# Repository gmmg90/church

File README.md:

# Controller Campane Chiesa — ESP32

Sistema completo per il controllo automatico delle campane di una chiesa, basato su ESP32 T-Display TS0636G. Supporta programmazione settimanale, eventi speciali, controllo remoto via bot Telegram, interfaccia Web, RTC DS3231 e due relè.

**Versione firmware: v2.3.10-unified-api**

---

## Caratteristiche principali

- Web UI moderna (SPIFFS) con schede: Stato, Melodie, Programmazione, Test Relè, Impostazioni
- Bot Telegram e API HTTP unificati su layer comune `CommandHandler` (stessa logica business)
- Display TFT integrato (T-Display 135×240) con ora, data e stato sistema
- Due melodie predefinite:
  - **FUNERALE** (slot 0): 30 colpi (campana 1×3 + 2×3), 300ms suono + 2700ms pausa
  - **CHIAMATA MESSA** (slot 1): scampanio fitto alternato 1–2, 300ms + 400ms, ~100 colpi (~40s)
- Editor melodie personalizzate (fino a 120 passi)
- Programmazione settimanale e per eventi speciali (matrimoni, fest, funerali…)
- Backup/ripristino configurazione in JSON
- Pulsanti fisici esterni: FUNERALE (GPIO27) e CHIAMATA MESSA (GPIO32)
- Protezione termica con stop automatico sopra 85°C
- WiFi keepalive non-bloccante con backoff esponenziale e recovery AP
- NTP re-sync automatico ogni ora, RTC DS3231 come fallback
- Factory reset via BOOT button (tieni premuto 10s)

---

## Hardware

| Componente | Pin/Note |
|---|---|
| ESP32 T-Display TS0636G | — |
| Display TFT ST7789V 135×240 | Gestito da TFT_eSPI (pinout in `platformio.ini`) |
| RTC DS3231 | SDA=GPIO21, SCL=GPIO22 (I2C) |
| Relè Campana 1 | GPIO25 — active-low (LOW=ON) |
| Relè Campana 2 | GPIO26 — active-low (LOW=ON) |
| LED Stato | GPIO2 (LED integrato ESP32) |
| LED Feedback Melodie | GPIO33 (LED esterno, opzionale) |
| BOOT Button / Config | GPIO0 |
| Pulsante Funerale | GPIO27 — collegare a GND |
| Pulsante Messa | GPIO32 — collegare a GND |

> **Nota pin GPIO33 per LED**: nella vecchia versione era GPIO23, che coincideva con il pin TFT_RST del display. Il pin è stato corretto a GPIO33.

---

## Installazione

### 1. Configurare le credenziali

Prima di compilare, modificare `src/config.cpp`:

```cpp
const char* WIFI_SSID     = "LA_TUA_RETE_WIFI";
const char* WIFI_PASSWORD = "LA_TUA_PASSWORD_WIFI";

// Token ottenuto da @BotFather su Telegram
const char* TELEGRAM_BOT_TOKEN = "IL_TUO_TOKEN_BOT_TELEGRAM";
```

> **IMPORTANTE**: Non committare mai credenziali reali su repository pubblici. Aggiungere `src/config.cpp` al `.gitignore` se necessario.

### 2. Aggiungere utenti Telegram autorizzati

In `src/config.cpp`:

```cpp
const char* TELEGRAM_AUTHORIZED_USERS[] = {
    "123456789",   // Il tuo Chat ID (usa /start sul bot per ottenerlo)
};
const uint8_t TELEGRAM_AUTHORIZED_COUNT = 1;
```

### 3. Build e upload

In VS Code (PlatformIO):

| Task | Azione |
|---|---|
| Build firmware | `PlatformIO Build` |
| Upload firmware | `PlatformIO Upload` |
| Upload Web UI (SPIFFS) | `PlatformIO Upload FS` |
| Monitor seriale | `PlatformIO Monitor` (115200 baud) |

CLI equivalente:
```powershell
pio run -e esp32dev
pio run -e esp32dev --target upload
pio run -e esp32dev --target uploadfs
```

### 4. Primo avvio

1. Collega l'ESP32 e carica il firmware + SPIFFS.
2. Se le credenziali WiFi non sono configurate (o la connessione fallisce per 5 tentativi), il dispositivo avvia un Access Point di recovery:
   - SSID: `ChurchBells-Config`
   - Password: `campanile123`
   - Apri `http://192.168.4.1` → scheda Impostazioni → configura WiFi.
3. Al riavvio, l'IP locale appare sul display TFT e in seriale.

---

## Configurazione (file principali)

### `src/config.cpp` — Credenziali (NON committare!)
- WiFi SSID e password
- Token bot Telegram
- Lista Chat ID autorizzati

### `src/include/config.h` — Costanti sistema

| Costante | Default | Descrizione |
|---|---|---|
| `WEB_SERVER_PORT` | 80 | Porta Web UI |
| `ADMIN_USER` | `admin` | Username Basic Auth Web UI |
| `ADMIN_PASSWORD` | `LA_TUA_PASSWORD_ADMIN` | Password Basic Auth Web UI |
| `MAX_MELODY_STEPS` | 120 | Max passi per melodia |
| `BELL_MIN_PULSE` | 100ms | Impulso minimo relè |
| `BELL_MAX_PULSE` | 2000ms | Impulso massimo relè |
| `TEMP_WARNING_THRESHOLD` | 70°C | Soglia avviso temperatura |
| `TEMP_SHUTDOWN_THRESHOLD` | 85°C | Soglia stop emergenza temperatura |

---

## Bot Telegram — Comandi

| Comando | Descrizione |
|---|---|
| `/start` | Benvenuto + info autorizzazione |
| `/help` | Lista comandi |
| `/status` | Stato sistema (campane, WiFi, temperatura, uptime) |
| `/enable` / `/attiva` | Attiva campane |
| `/disable` / `/disattiva` | Disattiva campane |
| `/ring <1\|2> <ms>` | Suona campana N per X millisecondi |
| `/funeral` / `/funerale` | Avvia scampanio funerale (slot 0) |
| `/mass` / `/messa` | Avvia chiamata messa (slot 1) |
| `/melody <0-9>` | Avvia melodia per indice |
| `/schedule` / `/orari` | Prossimi eventi programmati |
| `/time` | Mostra ora/data corrente dispositivo |
| `/ntp` | Forza una resincronizzazione NTP |
| `/backup` | Mostra stato e istruzioni backup |
| `/restore` | Mostra istruzioni ripristino backup |
| `/info` | Info firmware, heap, CPU |
| `/auth` | Richiedi autorizzazione (mostra il tuo Chat ID) |

Per aggiungere un utente: dalla Web UI → Impostazioni → Telegram, oppure aggiungere il Chat ID in `config.cpp` e ricompilare.

---

## Web UI

Aprire `http://<IP-dispositivo>`. Autenticazione Basic richiesta (username/password da `config.h`).

- **Stato**: ora/data, WiFi, RTC, NTP, campane ON/OFF, test mode, temperatura, uptime
- **Melodie**: lista, riproduzione/stop, editor note (bellNumber, duration, delay)
- **Programmazione**: settimanale e eventi speciali con "programmazione semplificata"
- **Test Relè**: attivazione manuale singoli relè con durata
- **Impostazioni**: WiFi, rete IP statico/DHCP, orario manuale, backup/ripristino JSON, Telegram

---

## API REST principali

Le API sotto usano lo stesso livello comandi del bot Telegram (`CommandHandler`) per garantire coerenza dei comportamenti.

| Endpoint | Metodo | Descrizione |
|---|---|---|
| `/api/status` | GET | Stato completo sistema |
| `/api/time` | GET | Ora/data corrente |
| `/api/melodies` | GET | Lista melodie |
| `/api/melody?index=N` | GET | Dettaglio melodia N |
| `/api/test-melody` | POST | Avvia melodia `{"melodyId": N}` |
| `/api/stop-melody` | GET/POST | Stop melodia in corso |
| `/api/save-melody` | POST | Salva nuova melodia |
| `/api/update-melody` | POST | Aggiorna melodia esistente |
| `/api/delete-melody` | POST | Elimina melodia |
| `/api/weekly-schedules` | GET/POST | Programmazioni settimanali |
| `/api/special-events` | GET/POST | Eventi speciali |
| `/api/toggle-bells` | GET/POST | Abilita/disabilita campane |
| `/api/test-relay` | POST | Test relè `?relay=1&duration=500` |
| `/api/emergency-stop` | POST | Stop emergenza |
| `/api/backup` | GET | Download backup JSON |
| `/api/restore` | POST | Ripristino da JSON |
| `/api/configure-wifi` | POST | Salva WiFi e riavvia |
| `/api/set-time` | POST | Imposta ora manuale |

---

## Sicurezza

- **Credenziali WiFi e token Telegram** non devono mai essere committati su repository pubblici. Modificare sempre `src/config.cpp` prima del deploy.
- **Web UI**: protetta da Basic Auth. Le credenziali di default (`admin`/`LA_TUA_PASSWORD_ADMIN`) devono essere cambiate prima del deploy in `src/include/config.h`.
- **Bot Telegram**: solo gli utenti con Chat ID esplicitamente autorizzati possono usare i comandi. I nuovi utenti devono usare `/auth` e aspettare approvazione manuale.
- **TLS Telegram**: la connessione a `api.telegram.org` usa HTTPS. La verifica del certificato è disabilitata per default (`setInsecure()`). Per abilitarla su una rete non fidata, aggiungere il certificato root DigiCert Global Root G2:
  ```bash
  # Ottieni il certificato
  openssl s_client -connect api.telegram.org:443 -showcerts
  ```
  Poi in `telegram_bot.cpp` sostituire `setInsecure()` con `_client.setCACert(TELEGRAM_ROOT_CA_PEM)`.
- **Rete locale**: se il dispositivo deve essere raggiungibile da Internet, proteggere con VPN o reverse proxy HTTPS. Non esporre mai la Web UI direttamente su porte pubbliche.

---

## Diagnostica

Comandi disponibili via Monitor Seriale (115200 baud):

| Comando | Descrizione |
|---|---|
| `wifi_diag` | Stato WiFi dettagliato (IP, RSSI, gateway, DNS) |
| `ntp_diag` | Stato NTP/RTC (drift, ultimo sync) |
| `full_diag` | Diagnostica completa sistema |
| `temp` | Temperatura ESP32 corrente |
| `schedules` | Lista programmazioni caricate |

---

## Risoluzione problemi

| Problema | Soluzione |
|---|---|
| UI non raggiungibile | Controlla IP su display, prova `/api/status`, verifica rete |
| RTC non rilevato | Controlla cablaggio SDA/SCL, scansiona I2C con `/api/i2c-scan` (atteso 0x68) |
| Campane non suonano via Telegram | Esegui `/enable` + `/status` per verificare lo stato |
| Pulsante funerale/messa non risponde | Verifica collegamento GPIO-GND, controlla log `[FUNERAL]`/`[MASS]` in seriale |
| Display TFT non funziona | Verifica pinout in `platformio.ini`, controlla TFT_RST=23 non in conflitto con altri GPIO |
| WDT reset | Evita payload enormi senza rete stabile; il watchdog si auto-alimenta ogni 100ms |
| Restore fallisce | Verifica validità JSON; il sistema traccia contatori `imported.*` nella risposta |
| Bot Telegram non risponde | Verifica token in `config.cpp`, controlla log `[Telegram]` in seriale |
| Ore legale/solare errata | L'ora è gestita automaticamente via POSIX TZ `CET-1CEST,M3.5.0/2,M10.5.0/3` |

### Factory Reset

Tenere premuto il pulsante BOOT (GPIO0) per 10 secondi. Cancella tutta la configurazione SPIFFS (WiFi, melodie, schedules). Il firmware rimane intatto.

---

## Changelog

| Versione | Novità |
|---|---|
| v2.3.10 | Unificazione Telegram + HTTP tramite `CommandHandler`, nuove azioni Telegram `/time` `/ntp` `/backup` `/restore` |
| v2.3.9 | Bot Telegram con autenticazione whitelist, comandi remoti campane |
| v2.3.8 | Sistema recovery multilivello: DHCP fallback, AP mode dopo 5 fail WiFi |
| v2.3.7 | Protezione picchi tensione, soft-start relè, LED feedback melodie (GPIO33) |
| v2.3.6 | Refactoring schedules unificati (schedules.json) |
| v2.3.5 | WatchdogManager, WiFiReconnectManager, gestione errori strutturata |
| v2.3.2 | Performance Web UI, ottimizzazioni memoria |
| v2.3.1 | Anti-flicker UI, throttling API, CSS anti-FOUC |
| v2.3.0 | WiFi keepalive 30s, NTP re-sync orario, fix melodie interrotte |

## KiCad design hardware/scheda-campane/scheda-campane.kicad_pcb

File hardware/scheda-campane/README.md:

# Scheda base campane v1.0 (T-Display + 24 V)

Circuito stampato 100 × 80 mm su cui si innesta il **LilyGO T-Display ESP32**. La scheda:

- si alimenta a **24 VDC**, con fusibile ripristinabile, protezione dall'inversione di polarità e soppressore di picchi (TVS); un convertitore DC-DC K7805-1000R3 (ingresso 8–36 V) ricava i 5 V;
- pilota **4 uscite a 24 V** tramite ULN2003: 2 campane più 2 di riserva, ciascuna con LED. Le uscite sono **spente** quando l'ESP32 è spento, in reset o in programmazione;
- legge **4 ingressi optoisolati a 24 V**: FUNERALE, MESSA e 2 di riserva, ciascuno con LED;
- ha l'**orologio DS3231M integrato** (stessi registri del DS3231: il firmware non cambia) con batteria tampone CR2032;
- ha uno **zoccolo per il T-Display** con l'USB-C sul bordo, per programmarlo senza smontarlo, e la zona dell'antenna WiFi senza rame.

Sulla scheda arrivano solo 24 V: **niente 230 V**. I 230 V restano nel quadro elettrico.

| Lato componenti | Montaggio |
|---|---|
|  |  |

Schema elettrico: [`docs/schema-elettrico.pdf`](docs/schema-elettrico.pdf). Controllo DRC: [`docs/drc-report.txt`](docs/drc-report.txt) (0 errori, 0 collegamenti mancanti).

## File

| File | A cosa serve |
|---|---|
| `produzione/scheda-campane-gerber-jlcpcb.zip` | Gerber + forature, da caricare su JLCPCB |
| `produzione/scheda-campane-BOM-jlcpcb.csv` | Distinta materiali con i codici LCSC |
| `produzione/scheda-campane-CPL-jlcpcb.csv` | Posizione e rotazione dei componenti per il montaggio |
| `scheda-campane.kicad_pro/.kicad_pcb/.kicad_sch` | Progetto KiCad (si apre con KiCad 7 o successivi) |
| `tools/` | Script che rigenerano tutto (vedi in fondo) |

## Ordinare su JLCPCB

1. Su jlcpcb.com scegli **Order now** e carica lo zip dei Gerber. Lascia le impostazioni standard: 2 strati, FR-4, 1,6 mm, rame 1 oz. Quantità minima: 5 schede.
2. Attiva **PCB Assembly**, lato **Top**, tipo **Standard**. Lo Standard serve perché ci sono componenti a foro passante: morsetti, connettori del T-Display e convertitore DC-DC. Scegli quante schede montare (minimo 2).
3. Carica la **BOM** e il **CPL**. JLCPCB abbina i componenti tramite la colonna `LCSC Part #`.
4. **Controlla l'anteprima del montaggio**, componente per componente. Per alcuni package lo zero di rotazione di JLCPCB è diverso da quello di KiCad. Se un componente appare ruotato, correggilo nell'anteprima con il tasto di rotazione. Verifica in particolare:
   - **D1, D3** (SS34), **D2** (SMBJ33A), **D4–D7** (1N4148W): la banda del catodo deve coincidere con la banda disegnata sulla serigrafia;
   - **LED1–LED10**: catodo verso il segno della serigrafia;
   - **U2** (ULN2003), **U7** (DS3231M), **U3–U6** (optoisolatori): il pallino del pin 1 sul segno del pin 1;
   - **BT1** (portabatteria CR2032).
5. La **batteria CR2032** non viene montata da JLCPCB: va comprata a parte e inserita.

Prima di ordinare, stampa `docs/scheda-montaggio.png` in **scala 1:1** (100 × 80 mm) e appoggia il T-Display sui due connettori, per controllare che le misure coincidano.

### Costi e come risparmiare

Componenti per 5 schede: circa **48 $** (circa 9,7 $ a scheda, prezzi JLCPCB di novembre 2026). Si aggiungono i 3 $ di caricamento per ogni tipo di componente "Extended" (8 tipi), il circuito stampato, il montaggio e la spedizione.

Per spendere ancora meno:
- **Saldare tu i componenti a foro passante**: morsetti J1–J9, connettori J10–J11 e convertitore U1, circa 30 saldature. Nella BOM di JLCPCB togli la spunta a queste righe e compra i pezzi su LCSC con gli stessi codici. Eviti il costo del montaggio manuale di JLCPCB e 3 tipi "Extended".
- **Non montare i canali di riserva**, se non ti servono: togli la spunta a J4, J5, J6, J7, R8, R9, LED4, LED5, U3, U4, R10, R11, LED6, LED7, D4, D5, R14, R15, C5, C6. Il resto della scheda funziona uguale.

## Collegamenti nel quadro

```
Alimentatore 24 VDC ──► J1 "+24V" / "0V"

USCITE (J2..J5)                      RELÈ D'INTERFACCIA 24 VDC (es. Finder 38.51)
  morsetto "+24V" ─────────────────► A1 (+)
  morsetto "OUT"  ─────────────────► A2 (−)
                                      11 (COM) ◄── L 230 V (dopo il fungo d'emergenza)
                                      14 (NA)  ──► A1 bobina teleruttore Schneider ── A2 ── N
                                                   (soppressore RC sulla bobina; varistore sul martello)

INGRESSI (J6..J9)
  morsetto "+24V" ── pulsante (contatto NA) ── morsetto "IN"
```

| Morsetto | Funzione | GPIO |
|---|---|---|
| J1 | Alimentazione 24 VDC | — |
| J2 | CAMPANA 1 | GPIO25 |
| J3 | CAMPANA 2 | GPIO26 |
| J4 | USCITA 3 (riserva) | GPIO33 |
| J5 | USCITA 4 (riserva) | GPIO17 |
| J9 | FUNERALE | GPIO27 |
| J8 | MESSA | GPIO32 |
| J6 | IN 3 (riserva) | GPIO36 |
| J7 | IN 4 (riserva) | GPIO39 |

Ogni uscita regge fino a 500 mA (corrente totale limitata dal fusibile da 1,1 A). I relè d'interfaccia da 24 V assorbono pochi mA.

## Firmware

Con questa scheda le uscite sono **attive HIGH** (in passato erano moduli relè attivi LOW). Compila e carica con l'ambiente dedicato:

```bash
pio run -e scheda_v1 --target upload
```

L'ambiente `esp32dev` resta per il vecchio cablaggio con moduli relè attivi LOW. Gli ingressi non cambiano: premendo il pulsante il GPIO va a livello basso, come prima.

## Avvertenze

- Il progetto ha superato il controllo automatico delle regole di KiCad (DRC) ed è stato verificato che schema e circuito stampato abbiano gli stessi collegamenti. **Non è ancora stato provato fisicamente**: ordina prima poche schede e collaudale. Una revisione da parte di un tecnico elettronico è consigliata.
- La parte a 230 V del quadro (teleruttori, relè d'interfaccia, fungo) va realizzata da un elettricista abilitato (DM 37/08).
- Le piste sono state tracciate da uno script automatico (`tools/router.py`). Il risultato è corretto elettricamente ma meno "elegante" di un tracciato fatto a mano. Puoi rifinirlo in KiCad.

## Rigenerare i file

Servono KiCad 7 (con `pcbnew` per Python e `kicad-cli`) e, per le immagini, Node.js con Playwright.

```bash
/usr/bin/python3 hardware/scheda-campane/tools/make.py
```

Lo script esegue: `board_def.py` (componenti, collegamenti, posizioni) → `build.py` (circuito stampato) → `router.py` (piste e piani di massa) → DRC → `export.py` (file JLCPCB) → `sch_gen.py` (schema) → verifica schema/PCB → immagini. Per modificare la scheda, cambia `board_def.py` e rilancia.

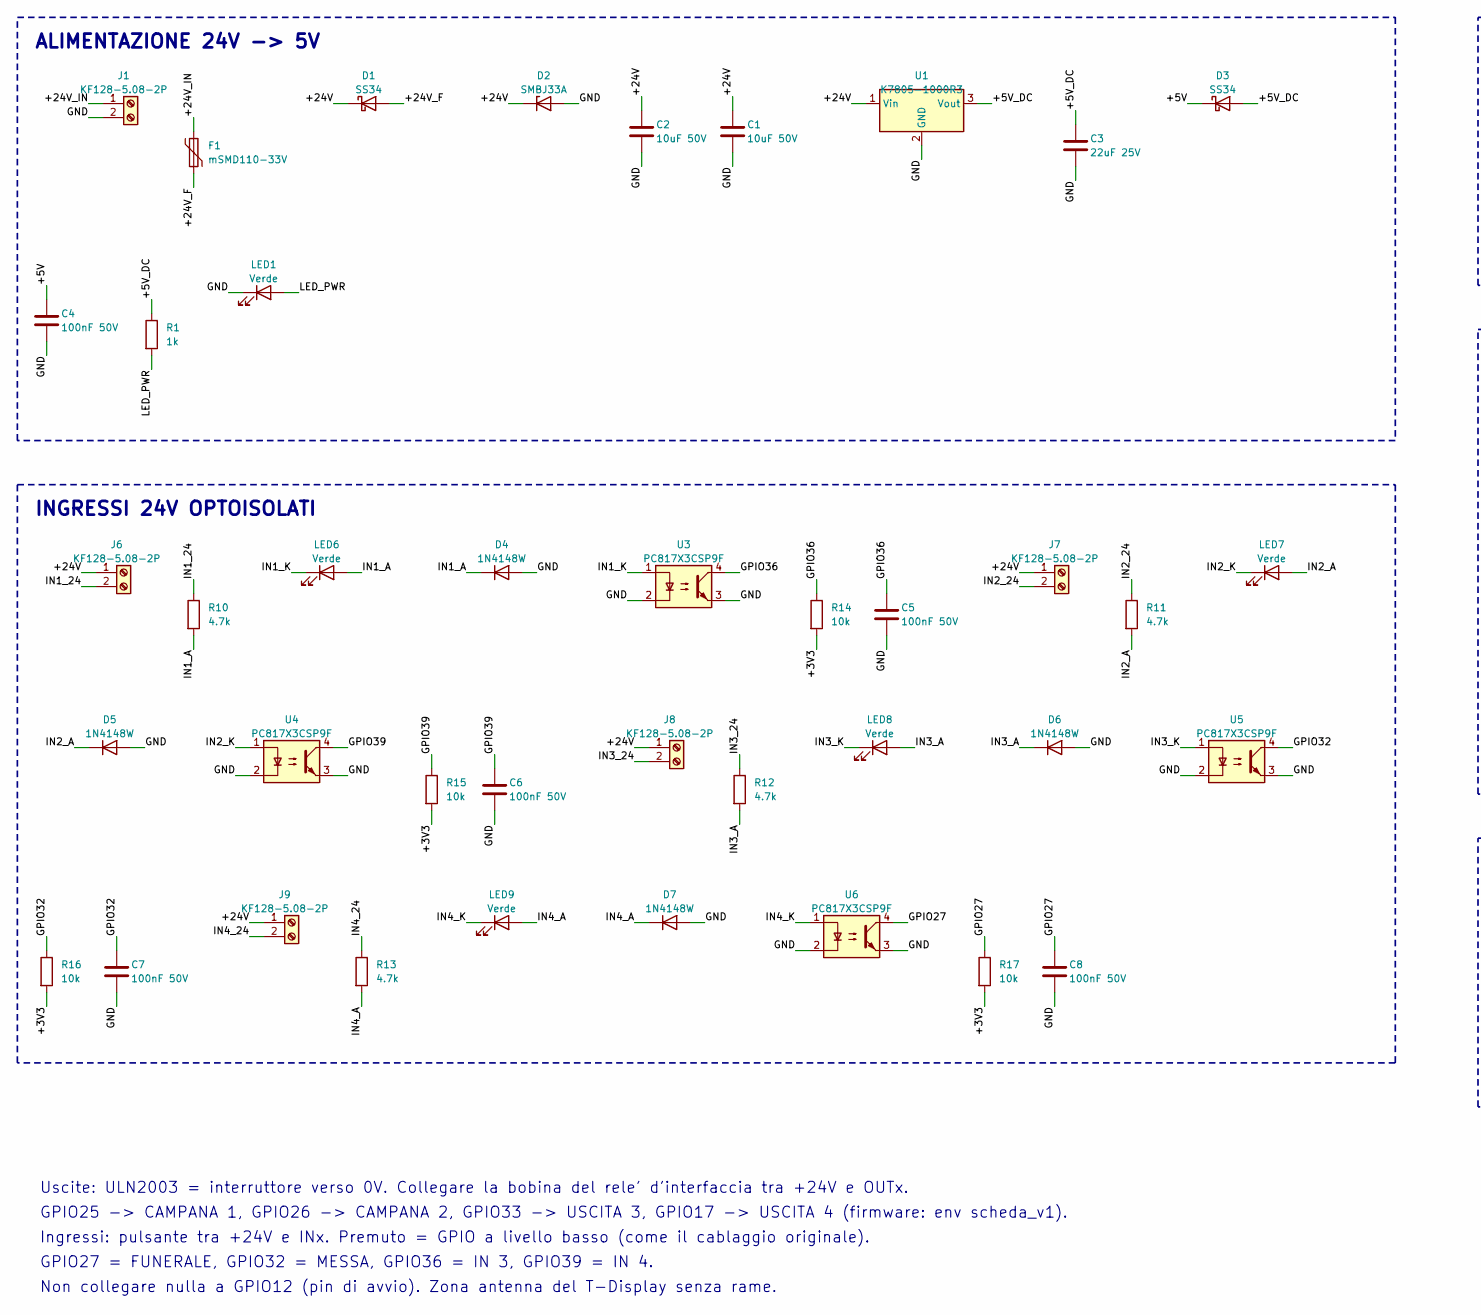
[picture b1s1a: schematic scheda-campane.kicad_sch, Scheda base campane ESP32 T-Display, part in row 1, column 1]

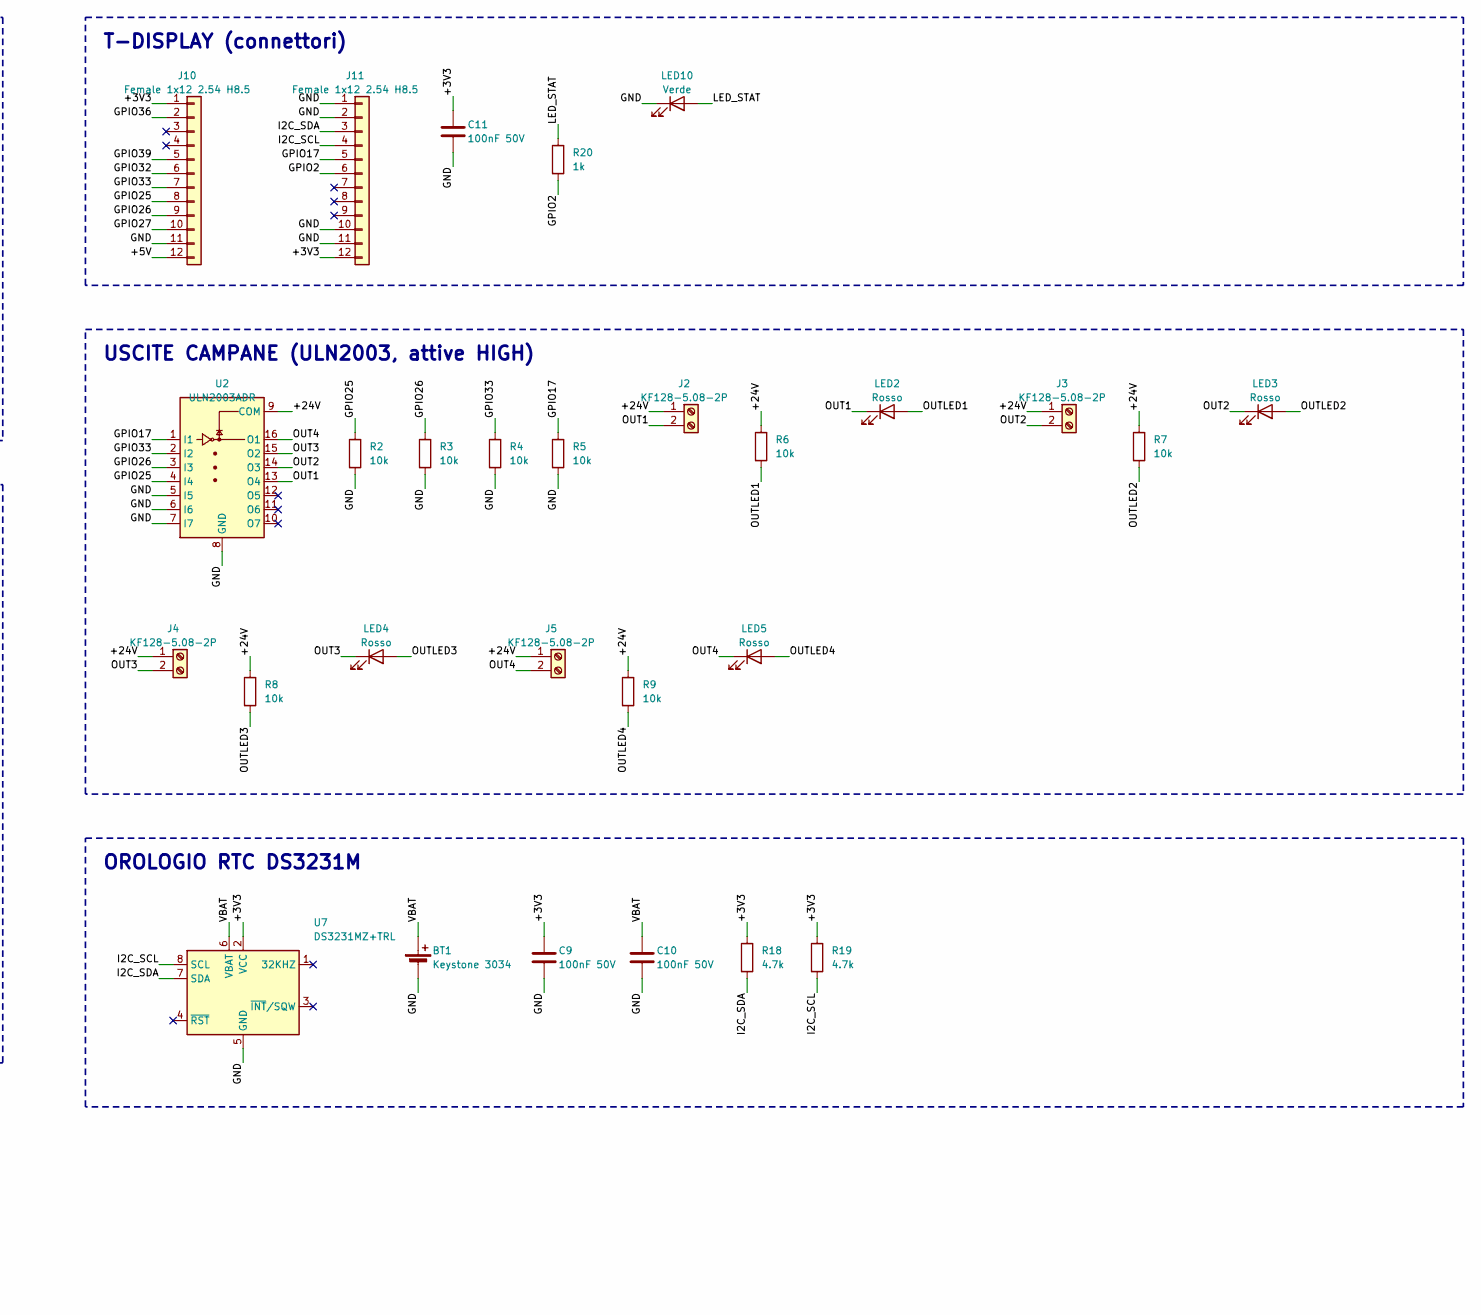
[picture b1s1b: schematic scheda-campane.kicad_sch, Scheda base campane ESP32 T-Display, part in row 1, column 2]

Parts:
BT1: Keystone 3034; BatteryHolder_Keystone_3034_1x20mm; LCSC C5213768
C1, C2: 10uF 50V; C_1206_3216Metric; LCSC C13585
C3: 22uF 25V; C_0805_2012Metric; LCSC C45783
C4, C5, C6, C7, C8, C9, C10, C11: 100nF 50V; C_0603_1608Metric; LCSC C14663
D1, D3: SS34; D_SMA; LCSC C8678
D2: SMBJ33A; D_SMB; LCSC C224019
D4, D5, D6, D7: 1N4148W; D_SOD-123; LCSC C81598
F1: mSMD110-33V; Fuse_1812_4532Metric; LCSC C70119
J1, J2, J3, J4, J5, J6, J7, J8, J9: KF128-5.08-2P; TerminalBlock_Phoenix_MKDS-1,5-2-5.08_1x02_P5.08mm_Horizont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; LCSC C474952
J10, J11: Female 1x12 2.54 H8.5; PinSocket_1x12_P2.54mm_Vertical; LCSC C22373898
LED1, LED6, LED7, LED8, LED9, LED10: Verde; LED_0805_2012Metric; LCSC C2297
LED2, LED3, LED4, LED5: Rosso; LED_0603_1608Metric; LCSC C2286
R1, R20: 1k; R_0603_1608Metric; LCSC C21190
R2, R3, R4, R5, R14, R15, R16, R17: 10k; R_0603_1608Metric; LCSC C25804
R6, R7, R8, R9: 10k; R_0805_2012Metric; LCSC C17414
R10, R11, R12, R13: 4.7k; R_1206_3216Metric; LCSC C17936
R18, R19: 4.7k; R_0603_1608Metric; LCSC C23162
U1: K7805-1000R3; Converter_DCDC_RECOM_R-78E-0.5_THT; LCSC C2992391
U2: ULN2003ADR; SOIC-16_3.9x9.9mm_P1.27mm; LCSC C7512
U3, U4, U5, U6: PC817X3CSP9F; SMDIP-4_W9.53mm; LCSC C41807
U7: DS3231MZ+TRL; SOIC-8_3.9x4.9mm_P1.27mm; LCSC C107410

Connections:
+3V3: C9.1, C11.1, J10.1, J11.12, R14.2, R15.2, R16.2, R17.2, R18.1, R19.1, U7.2 (VCC)
+5V: C4.1, D3.1 (K), J10.12
+5V_DC: C3.1, D3.2 (A), R1.1, U1.3 (Vout)
+24V: C1.1, C2.1, D1.1 (K), D2.1 (K), J2.1, J3.1, J4.1, J5.1, J6.1, J7.1, J8.1, J9.1, R6.1, R7.1, R8.1, R9.1, U1.1 (Vin), U2.9 (COM)
+24V_F: D1.2 (A), F1.2
+24V_IN: F1.1, J1.1
GND: BT1.2 (-), C1.2, C2.2, C3.2, C4.2, C5.2, C6.2, C7.2, C8.2, C9.2, C10.2, C11.2, D2.2 (A), D4.2 (A), D5.2 (A), D6.2 (A), D7.2 (A), J1.2, J10.11, J11.1, J11.2, J11.10, J11.11, LED1.1 (K), LED10.1 (K), R2.2, R3.2, R4.2, R5.2, U1.2 (GND), U2.5 (I5), U2.6 (I6), U2.7 (I7), U2.8 (GND), U3.2, U3.3, U4.2, U4.3, U5.2, U5.3, U6.2, U6.3, U7.5 (GND)
GPIO2: J11.6, R20.2
GPIO17: J11.5, R5.1, U2.1 (I1)
GPIO25: J10.8, R2.1, U2.4 (I4)
GPIO26: J10.9, R3.1, U2.3 (I3)
GPIO27: C8.1, J10.10, R17.1, U6.4
GPIO32: C7.1, J10.6, R16.1, U5.4
GPIO33: J10.7, R4.1, U2.2 (I2)
GPIO36: C5.1, J10.2, R14.1, U3.4
GPIO39: C6.1, J10.5, R15.1, U4.4
I2C_SCL: J11.4, R19.2, U7.8 (SCL)
I2C_SDA: J11.3, R18.2, U7.7 (SDA)
IN1_24: J6.2, R10.1
IN1_A: D4.1 (K), LED6.2 (A), R10.2
IN1_K: LED6.1 (K), U3.1
IN2_24: J7.2, R11.1
IN2_A: D5.1 (K), LED7.2 (A), R11.2
IN2_K: LED7.1 (K), U4.1
IN3_24: J8.2, R12.1
IN3_A: D6.1 (K), LED8.2 (A), R12.2
IN3_K: LED8.1 (K), U5.1
IN4_24: J9.2, R13.1
IN4_A: D7.1 (K), LED9.2 (A), R13.2
IN4_K: LED9.1 (K), U6.1
LED_PWR: LED1.2 (A), R1.2
LED_STAT: LED10.2 (A), R20.1
OUT1: J2.2, LED2.1 (K), U2.13 (O4)
OUT2: J3.2, LED3.1 (K), U2.14 (O3)
OUT3: J4.2, LED4.1 (K), U2.15 (O2)
OUT4: J5.2, LED5.1 (K), U2.16 (O1)
OUTLED1: LED2.2 (A), R6.2
OUTLED2: LED3.2 (A), R7.2
OUTLED3: LED4.2 (A), R8.2
OUTLED4: LED5.2 (A), R9.2
VBAT: BT1.1 (+), C10.1, U7.6 (VBAT)

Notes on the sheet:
ALIMENTAZIONE 24V -> 5V
INGRESSI 24V OPTOISOLATI
T-DISPLAY (connettori)
USCITE CAMPANE (ULN2003, attive HIGH)
OROLOGIO RTC DS3231M
Uscite: ULN2003 = interruttore verso 0V. Collegare la bobina del rele' d'interfaccia tra +24V e OUTx.
GPIO25 -> CAMPANA 1, GPIO26 -> CAMPANA 2, GPIO33 -> USCITA 3, GPIO17 -> USCITA 4 (firmware: env scheda_v1).
Ingressi: pulsante tra +24V e INx. Premuto = GPIO a livello basso (come il cablaggio originale).
GPIO27 = FUNERALE, GPIO32 = MESSA, GPIO36 = IN 3, GPIO39 = IN 4.
Non collegare nulla a GPIO12 (pin di avvio). Zona antenna del T-Display senza rame.

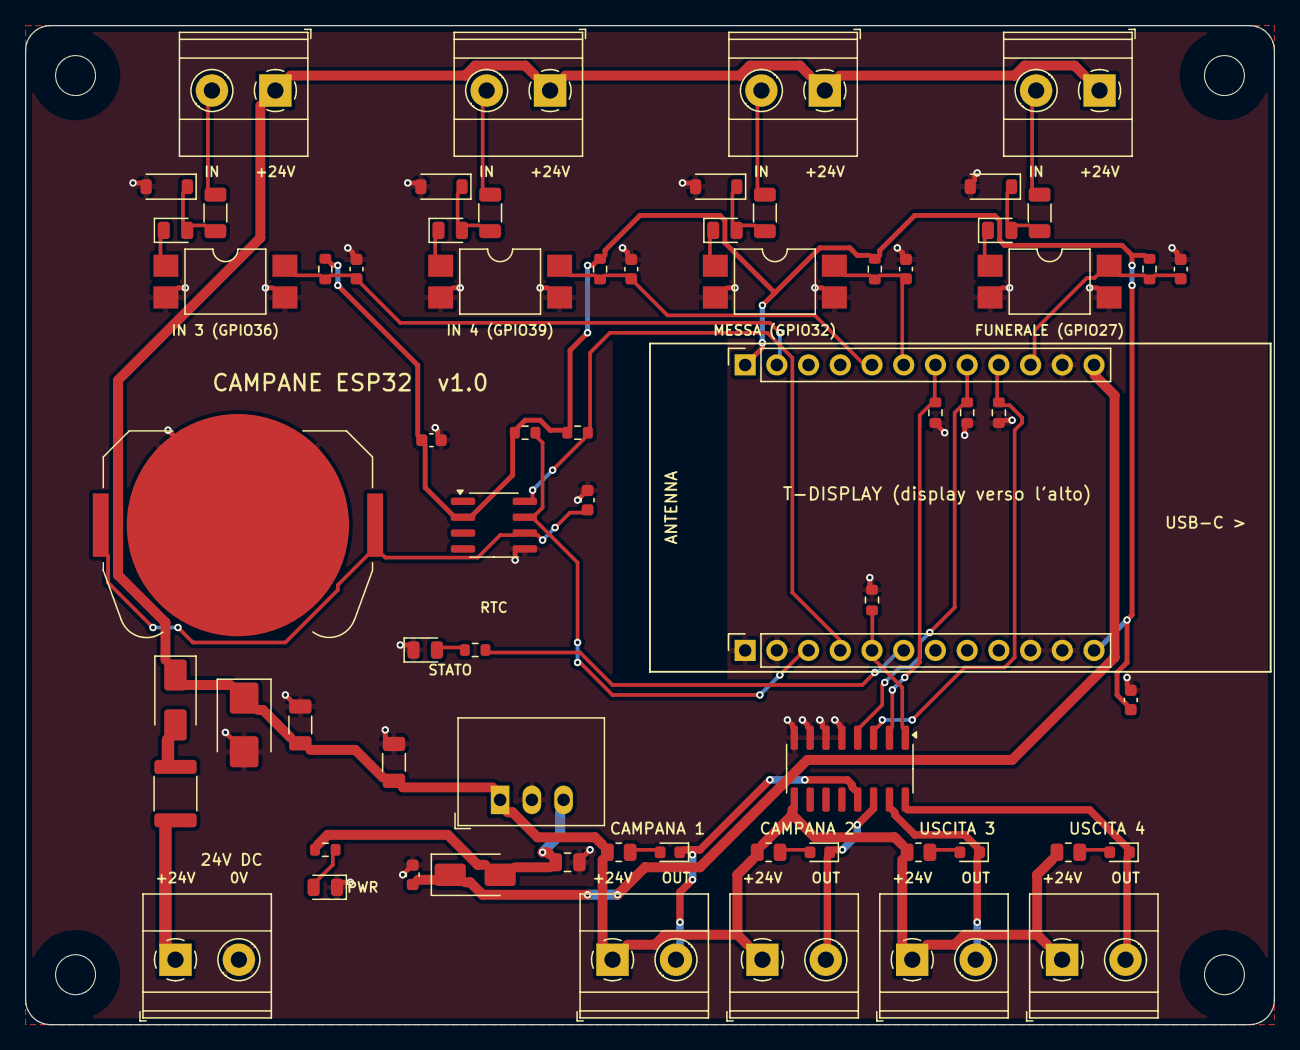
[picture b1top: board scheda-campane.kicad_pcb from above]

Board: 2 copper layers, 100.0 x 80.0 mm, 72 parts (0 on the bottom side), 41 nets.

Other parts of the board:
MH1, MH2, MH3, MH4: M3; MountingHole_3.2mm_M3

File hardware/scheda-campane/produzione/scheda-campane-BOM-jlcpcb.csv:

Comment,Designator,Footprint,LCSC Part #,Quantity,Descrizione
Keystone 3034,BT1,BatteryHolder_Keystone_3034_1x20mm,C5213768,1,Portabatteria CR2032 SMD
10uF 50V,"C1,C2",C_1206_3216Metric,C13585,2,Condensatore ceramico 10 uF 50 V X5R (1206)
22uF 25V,C3,C_0805_2012Metric,C45783,1,Condensatore ceramico 22 uF 25 V X5R (0805)
100nF 50V,"C4,C5,C6,C7,C8,C9,C10,C11",C_0603_1608Metric,C14663,8,Condensatore ceramico 100 nF 50 V X7R (0603)
SS34,"D1,D3",D_SMA,C8678,2,Diodo Schottky 3 A 40 V (SMA)
SMBJ33A,D2,D_SMB,C224019,1,Diodo TVS 600 W 33 V unidirezionale (SMB)
1N4148W,"D4,D5,D6,D7",D_SOD-123,C81598,4,Diodo di segnale (SOD-123)
mSMD110-33V,F1,Fuse_1812_4532Metric,C70119,1,"Fusibile ripristinabile 1,1 A 33 V (1812)"
KF128-5.08-2P,"J1,J2,J3,J4,J5,J6,J7,J8,J9","TerminalBlock_Phoenix_MKDS-1,5-2-5.08_1x02_P5.08mm_Horizontal",C474952,9,"Morsetto a vite 2 poli passo 5,08 mm"
Female 1x12 2.54 H8.5,"J10,J11",PinSocket_1x12_P2.54mm_Vertical,C22373898,2,"Connettore femmina 1x12 passo 2,54 mm, h 8,5 mm, dorato"
Verde,"LED1,LED6,LED7,LED8,LED9,LED10",LED_0805_2012Metric,C2297,6,LED verde (0805)
Rosso,"LED2,LED3,LED4,LED5",LED_0603_1608Metric,C2286,4,LED rosso (0603)
1k,"R1,R20",R_0603_1608Metric,C21190,2,Resistenza 1 kOhm 1% (0603)
10k,"R2,R3,R4,R5,R14,R15,R16,R17",R_0603_1608Metric,C25804,8,Resistenza 10 kOhm 1% (0603)
10k,"R6,R7,R8,R9",R_0805_2012Metric,C17414,4,Resistenza 10 kOhm 1% (0805)
4.7k,"R10,R11,R12,R13",R_1206_3216Metric,C17936,4,"Resistenza 4,7 kOhm 1% 0,25 W (1206)"
4.7k,"R18,R19",R_0603_1608Metric,C23162,2,"Resistenza 4,7 kOhm 1% (0603)"
K7805-1000R3,U1,Converter_DCDC_RECOM_R-78E-0.5_THT,C2992391,1,"Convertitore DC-DC 24 V -> 5 V 1 A, ingresso 8-36 V (YLPTEC)"
ULN2003ADR,U2,SOIC-16_3.9x9.9mm_P1.27mm,C7512,1,Driver Darlington 7 canali (SOIC-16)
PC817X3CSP9F,"U3,U4,U5,U6",SMDIP-4_W9.53mm,C41807,4,Optoisolatore (SMD-4)
DS3231MZ+TRL,U7,SOIC-8_3.9x4.9mm_P1.27mm,C107410,1,RTC di precisione I2C DS3231M (SOIC-8)

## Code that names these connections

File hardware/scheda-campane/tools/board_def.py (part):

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add("LED1", "LED0805", "LEDG", 24.0, 69.0, 180, {"2": "LED_PWR", "1": "GND"})

# ------------------------------------------------------------------ T-Display
UP_NETS = ["+3V3", "GPIO36", None, None, "GPIO39", "GPIO32", "GPIO33",
           "GPIO25", "GPIO26", "GPIO27", "GND", "+5V"]
LO_NETS = ["GND", "GND", "I2C_SDA", "I2C_SCL", "GPIO17", "GPIO2", None,
           None, None, "GND", "GND", "+3V3"]
add("J10", "SOCK12", "SOCK12", HDR_X, HDR_UP_Y, 90,
    {str(i + 1): n for i, n in enumerate(UP_NETS) if n})
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# ------------------------------------------------------------------ Uscite (ULN2003)
# ULN canale k: ingresso pin k, uscita pin 17-k
add("U2", "SOIC16", "ULN", 66.0, 59.5, 270, {
    "1": "GPIO17", "2": "GPIO33", "3": "GPIO26", "4": "GPIO25",
    "5": "GND", "6": "GND", "7": "GND", "8": "GND", "9": "+24V",
    "13": "OUT1", "14": "OUT2", "15": "OUT3", "16": "OUT4"})
# pull-down sotto il T-Display, vicino ai rispettivi pin (tengono spente le uscite a ESP32 spento)
for ref, x, y, rot, gpio in (("R2", HDR_X + 7 * 2.54, 31.0, 270, "GPIO25"),
                             ("R3", HDR_X + 8 * 2.54, 31.0, 270, "GPIO26"),
                             ("R4", HDR_X + 6 * 2.54, 31.0, 270, "GPIO33"),
                             ("R5", HDR_X + 4 * 2.54, 46.0, 90, "GPIO17")):
    add(ref, "R0603", "R10k", x, y, rot, {"1": gpio, "2": "GND"})

OUTPUTS = [  # terminale, x pin1, resistenza LED, LED, net, etichetta
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
# ------------------------------------------------------------------ Ingressi optoisolati
INPUTS = [  # x0 cella, terminale, R ingresso, LED, diodo, opto, pull-up, C, nome, gpio
    (8.0, "J6", "R10", "LED6", "D4", "U3", "R14", "C5", "IN 3", "GPIO36"),
    (30.0, "J7", "R11", "LED7", "D5", "U4", "R15", "C6", "IN 4", "GPIO39"),
    (52.0, "J8", "R12", "LED8", "D6", "U5", "R16", "C7", "MESSA", "GPIO32"),
    (74.0, "J9", "R13", "LED9", "D7", "U6", "R17", "C8", "FUNERALE", "GPIO27"),
]
for k, (x0, jref, rin, led, dio, opto, rpu, cf, _name, gpio) in enumerate(INPUTS, start=1):
    n24, na, nk = f"IN{k}_24", f"IN{k}_A", f"IN{k}_K"
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add("R19", "R0603", "R4k7", 44.2, 32.6, 0, {"1": "+3V3", "2": "I2C_SCL"})

# ------------------------------------------------------------------ LED di stato e 3V3
add("R20", "R0603", "R1k", 36.0, 50.0, 0, {"1": "LED_STAT", "2": "GPIO2"})
add("LED10", "LED0805", "LEDG", 32.0, 50.0, 0, {"2": "LED_STAT", "1": "GND"})
add("C11", "C0603", "C100n", 88.5, 54.0, 90, {"1": "+3V3", "2": "GND"})

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
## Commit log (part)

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2025-09-29 First Release
2025-10-06 Create Manuale da Stampare
2025-10-18 aumento array melodie settimanali a 64
2026-06-14 Fix 10 bugs critici: relay stuck, oscillazione pulsante, sicurezza hardware
    RELAY / SICUREZZA HARDWARE:
    - BellController: sposta bellActive/bellStartTime/bellDuration/activeBell
    da variabili static locali in update() a membri della classe, così
    emergencyStop() può azzerarle correttamente
    - emergencyStop(): aggiunge bellActive=false e bellDuration=0 per garantire
    che update() non tenti di gestire un relay già spento
2026-06-14 Redesign web UI with modern dark gold theme
    Complete visual overhaul of the control panel:
    - Dark charcoal background with gold/amber accent color scheme
    - Sticky header with animated bell icon, live clock, and LED status dots
    - Pill-style tab navigation with golden active state
    - Glassmorphism cards with subtle backdrop blur
    - Large Space Mono clock display on dashboard
2026-06-14 Add Telegram bot integration, API tester, and system logs
    ## Telegram Bot
    - TelegramBotController class with HTTP polling (no external library)
    Uses HTTPClient + WiFiClientSecure + ArduinoJson already in project
    - Commands: /stato, /melodie, /suona N, /funerale, /messa, /stop,
    /campane on|off, /test 1|2, /log, /chatid, /start /help
    - Inline keyboard with quick-action buttons (FUNERALE, MESSA, STOP...)
